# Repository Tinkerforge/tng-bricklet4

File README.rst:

TNG Bricklet4
=============

TBD

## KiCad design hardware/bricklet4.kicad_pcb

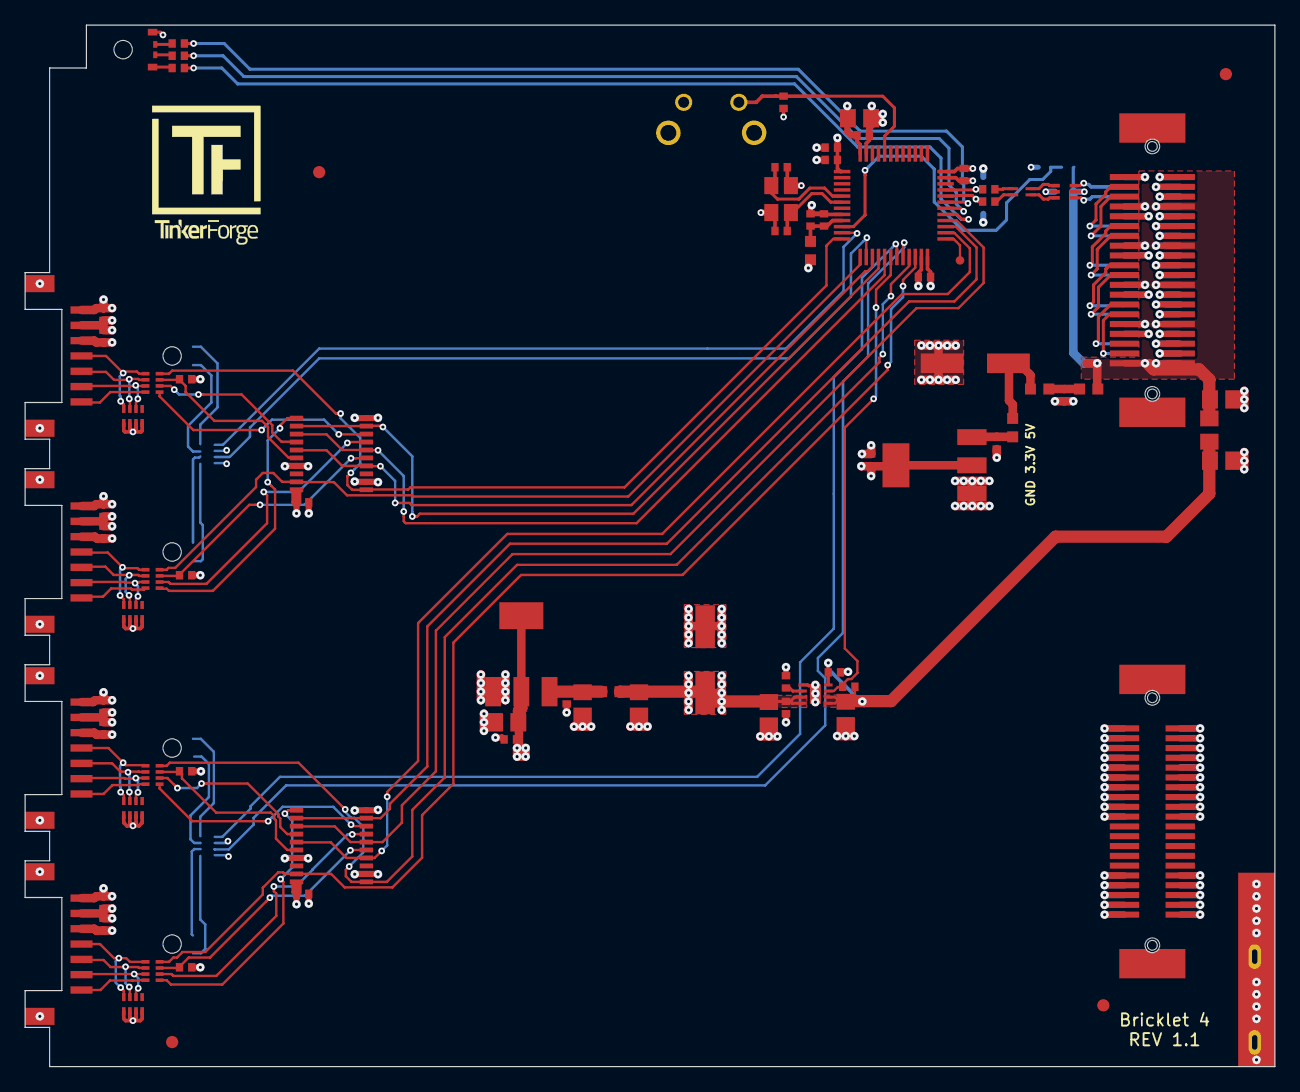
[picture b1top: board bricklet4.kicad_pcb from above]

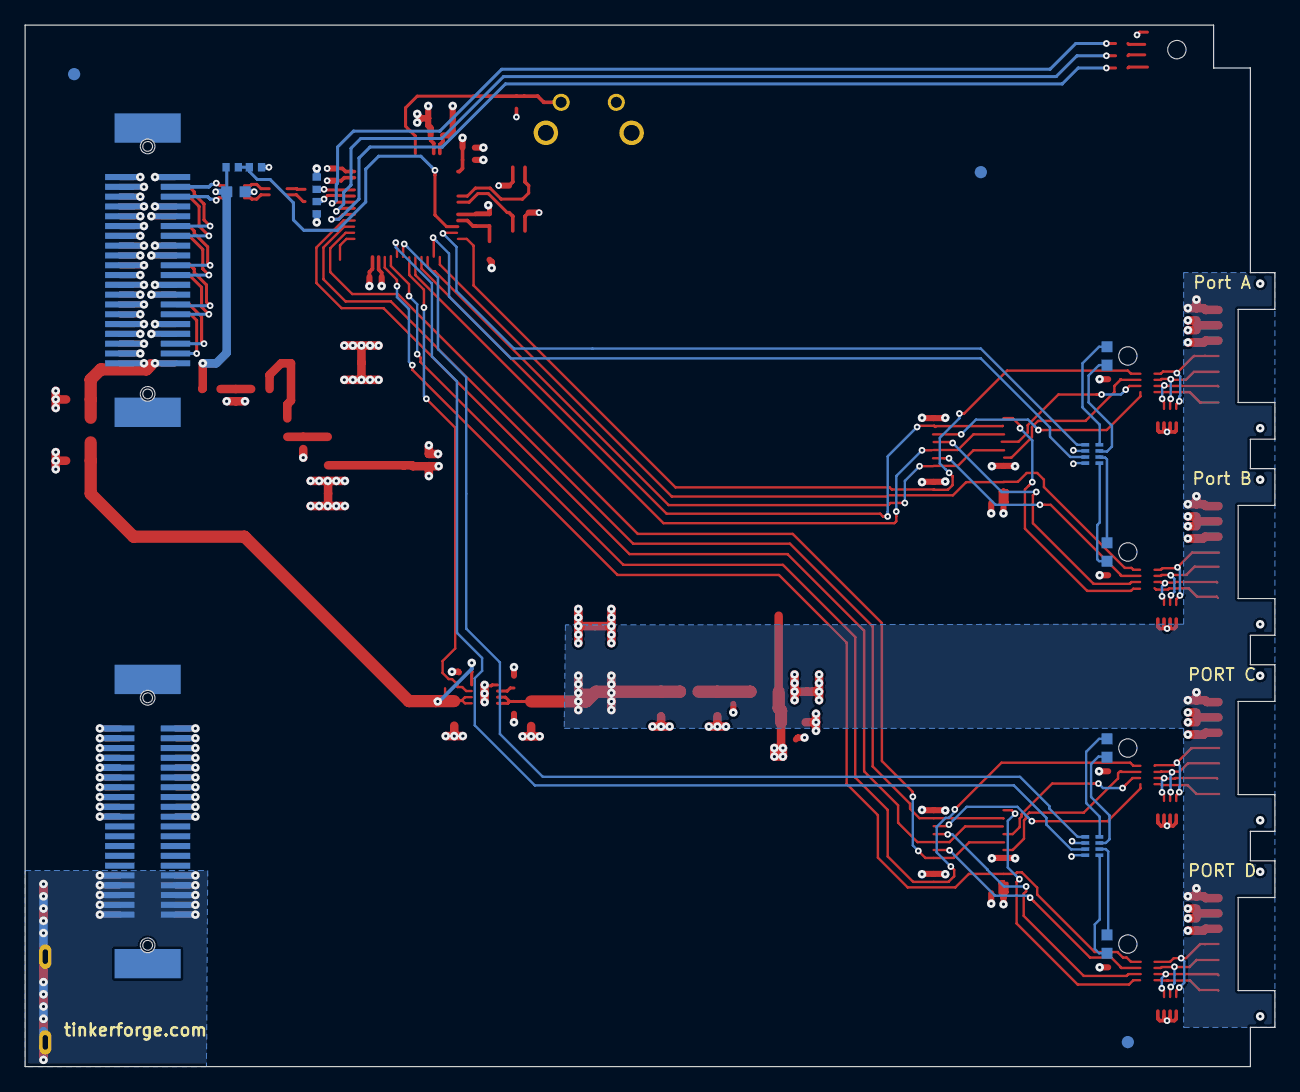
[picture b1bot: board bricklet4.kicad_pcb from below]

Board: 4 copper layers, 102.0 x 85.0 mm, 101 parts (16 on the bottom side), 93 nets.

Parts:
C101, C102, C116, C117, C205, C212, C213, C214, C215, C216, C217, C218, C219, C220, C221: 1uF; C0402F
C103, C104, C105, C106, C107, C112, C201, C202, C208: 100nF; C0402F
C108, C109: 33pF; C0402F
C110, C203, C204, C207, C210, C211, C222, C223: 10uF; C0805E
C111, C209: 100uF; ELKO_63
C113, C114: 47pF; C0402F
C115: 2.2uF; C0603F
C206: DNP; C0402F
CP201, CP202, CP203, CP204: 220pF; 4X0402
D201, D202, D203, D204: LED; LED-LP
Fiducial_Mark: VAL**; Fiducial_Mark
Fiducial_Mark#2, Fiducial_Mark#3, Fiducial_Mark#4, Fiducial_Mark#5, Fiducial_Mark#6, Fiducial_Mark#7: VAL**; Fiducial_Mark
J101: TNG-Power-TOP; TNG-40-TOP
J102: TNG-Power-BTM; TNG-40-BTM
J103: TNG-Data-TOP; TNG-40-TOP
J104: TNG-Data-BTM; TNG-40-BTM
L101: FB; R0603F
L102, L103, L104, L202: INDUCTs; R0603F
L105: 744230900; WE-CNSW-0603
L201: 742792040; R0805E
LED101: EASV3015RGBA0; LED-RGB-LP
P102: Debug; DEBUG_PAD
P103: PE; PE_Hook
P201, P202, P203, P204: CON-SENSOR2
R101, R107, R108: 1k; R0402F
R102, R105: 0; R0402F
R103, R104: 22; R0402F
R106: 56; R0402F
R201, R202, R203, R204, R205: 10k; R0402F
RP201, RP202, RP203, RP204: 82; 4X0402
RP205, RP206: 470; 4X0402
SW101: BOOT; TACT-6MM-HOR
U101: STM32F070CBT6; LQFP48
U102, U204: AZ1117EH; SOT-223
U103: 82400152; SOT563-SPEC
U201, U202: 74AHC244; TSSOP20
U203: TPS22975; WSON8-2x2
X101: 8MHz; CRYSTAL_3225

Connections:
3V3: C101.1, C103.1, C104.1, C105.1, C106.1, C110.1, C116.1, L101.1, LED101.1, RP205.2, RP205.4, RP206.2, RP206.4, SW101.1, U101.1, U101.24, U101.36, U101.48, U102.2
5VA: C115.1, C203.2, J103.7, J103.8, J103.15, J103.16, J103.23, J103.24, J103.31, J103.32, J103.39, J103.40, J104.7, J104.8, J104.15, J104.16, J104.23, J104.24, J104.31, J104.32, J104.39, J104.40, L104.1, L201.2, R107.1, U103.5
+5V: C111.1, L102.1, L103.2
AGNDA: J101.2, J101.4, J101.6, J101.8, J101.10, J101.12, J101.14, J101.16, J101.18, J101.20, J102.1, J102.3, J102.5, J102.7, J102.9, J102.11, J102.13, J102.15, J102.17, J102.19
AIN0: R107.2, R108.1, U101.10
B0-CLK: U101.15, U201.4, U201.15
B0-CS0: RP201.8, U101.12, U201.1
B0-CS1: RP202.8, U101.13, U201.19
B0-MISO: U101.16, U201.9, U201.12
B0-MOSI: U101.17, U201.6, U201.13
B1-CLK: U101.26, U202.4, U202.15
B1-CS0: RP203.8, U101.21, U202.1
B1-CS1: RP204.8, U101.22, U202.19
B1-MISO: U101.27, U202.9, U202.12
B1-MOSI: U101.28, U202.6, U202.13
B-3V3: C201.2, C202.2, C213.1, C215.1, C217.1, C219.1, C221.2, C222.2, P201.3, P202.3, P203.3, P204.3, R201.1, R202.1, R203.1, R204.1, U201.20, U202.20, U204.2
B-5V: C207.2, C208.2, C209.1, C210.2, C212.1, C214.1, C216.1, C218.1, L202.1, P201.1, P202.1, P203.1, P204.1, U203.7, U203.8
B-EN: R205.2, U101.18, U203.3
Earth: J101.31, J101.32, J101.33, J101.34, J101.35, J101.36, J101.37, J101.38, J101.39, J101.40, J102.31, J102.32, J102.33, J102.34, J102.35, J102.36, J102.37, J102.38, J102.39, J102.40, P103.1
GND: C101.2, C102.2, C103.2, C104.2, C105.2, C106.2, C107.2, C108.1, C109.1, C110.2, C111.2, C112.2, C113.2, C114.2, C115.2, C116.2, C117.2, C201.1, C202.1, C203.1, C204.1, C205.1, C206.1, C207.1, C208.1, C209.2, C210.1, C211.1, C212.2, C213.2, C214.2, C215.2, C216.2, C217.2, C218.2, C219.2, C220.1, C221.1, C222.1, C223.1, CP201.5, CP201.6, CP201.7, CP201.8, CP202.5, CP202.6, CP202.7, CP202.8, CP203.5, CP203.6, CP203.7, CP203.8, CP204.5, CP204.6, CP204.7, CP204.8, J103.1, J103.2, J103.4, J103.6, J103.9, J103.10, J103.12, J103.14, J103.17, J103.18, J103.20, J103.22, J103.25, J103.26, J103.28, J103.30, J103.33, J103.34, J103.36, J103.38, J104.1, J104.2, J104.3, J104.5, J104.9, J104.10, J104.11, J104.13, J104.17, J104.18, J104.19, J104.21, J104.25, J104.26, J104.27, J104.29, J104.33, J104.34, J104.35, J104.37, P201.2, P201.EP, P202.2, P202.EP, P203.2, P203.EP, P204.2, P204.EP, R101.1, R108.2, U101.8, U101.23, U101.35, U101.47, U102.1, U103.2, U201.2, U201.10, U201.17, U202.2, U202.10, U202.17, U203.5, U203.EXP, U204.1, X101.3
LED-A: RP205.1, U101.11
LED-B: RP205.3, U101.14
LED-C: RP206.1, U101.19
LED-D: RP206.3, U101.20
LEDB: R106.1, U101.31
LEDG: R105.1, U101.30
LEDR: R102.1, U101.29
unnamed: C102.1, C107.1, L101.2, U101.9
unnamed: C108.2, U101.5, X101.2
unnamed: C109.2, U101.6, X101.1
unnamed: C112.1, L103.1, L104.2
unnamed: C117.1, L102.2, U102.3
unnamed: C206.2, U203.6
unnamed: C211.2, C220.2, L202.2, U204.3
unnamed: CP201.2, P201.6, RP201.3
unnamed: CP201.3, P201.5, RP201.2
unnamed: CP201.4, P201.4, RP201.1
unnamed: CP202.2, P202.6, RP202.3
unnamed: CP202.3, P202.5, RP202.2
unnamed: CP202.4, P202.4, RP202.1
unnamed: CP203.2, P203.6, RP203.3
unnamed: CP203.3, P203.5, RP203.2
unnamed: CP203.4, P203.4, RP203.1
unnamed: CP204.2, P204.6, RP204.3
unnamed: CP204.3, P204.5, RP204.2
unnamed: CP204.4, P204.4, RP204.1
unnamed: D201.1, RP205.7
unnamed: D201.2, RP205.8
unnamed: D202.1, RP205.5
unnamed: D202.2, RP205.6
unnamed: D203.1, RP206.7
unnamed: D203.2, RP206.8
unnamed: D204.1, RP206.5
unnamed: D204.2, RP206.6
unnamed: J103.3, J104.12
unnamed: J103.5, J104.14
unnamed: J103.11, J104.20
unnamed: J103.13, J104.22
unnamed: J103.19, J104.28
unnamed: J103.21, J104.30
unnamed: J103.27, J104.36
unnamed: J103.29, J104.38
unnamed: LED101.2, R106.2
unnamed: LED101.3, R105.2
unnamed: LED101.4, R102.2
unnamed: P102.1, U101.25
unnamed: P201.7, RP201.4
unnamed: P202.7, RP202.4
unnamed: P203.7, RP203.4
unnamed: P204.7, RP204.4
unnamed: R101.2, SW101.2, U101.44
unnamed: R201.2, RP201.7, U201.16
unnamed: R202.2, RP202.7, U201.5
unnamed: R203.2, RP203.7, U202.16
unnamed: R204.2, RP204.7, U202.5
unnamed: RP201.5, U201.8
unnamed: RP201.6, U201.14
unnamed: RP202.5, U201.11
unnamed: RP202.6, U201.7
unnamed: RP203.5, U202.8
unnamed: RP203.6, U202.14
unnamed: RP204.5, U202.11
unnamed: RP204.6, U202.7
USB-DM: C114.1, R104.2, U101.32
USB-DMA: J104.6, U103.4
USB-DMB: L105.1, U103.3
USB-DMC: L105.2, R104.1
USB-DP: C113.1, R103.2, U101.33
USB-DPA: J104.4, U103.6
USB-DPB: L105.4, U103.1
USB-DPC: L105.3, R103.1
VCCPWRA: J101.1, J101.3, J101.5, J101.7, J101.9, J101.11, J101.13, J101.15, J101.17, J101.19, J102.2, J102.4, J102.6, J102.8, J102.10, J102.12, J102.14, J102.16, J102.18, J102.20
_B-5V: C204.2, C205.2, C223.2, L201.1, R205.1, U203.1, U203.2, U203.4

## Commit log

2020-06-24 initial checkin
2020-08-17 fix slew rate bug, mark C as DNP
2020-09-04 version 1.1
    fix footprints
2020-09-04 update tbd
2020-09-07 specify capacitors
2020-09-07 fix values
2020-09-08 fix footprint
2020-09-08 all footprints updated
2020-09-10 fix 3d stuff

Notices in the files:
hardware/bricklet4.kicad_pcb:
Licensed under CERN OHL v.1.1
Copyright (©) 2020, B.Nordmeyer
Copyright Tinkerforge GmbH 2020.
This documentation describes Open Hardware and is licensed under the
CERN OHL v. 1.1.
